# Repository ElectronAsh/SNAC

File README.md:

# SNAC
Accessory converter for MiSTer, by blue212

Serial Native Accessory Converter

SNAC is general purpose level shifter for use with MiSTer. It can be used to power 5v devices and it will safely convert any logic between the 3v3(MiSTer) and 5 device. It will be used mostly for 5v controllers and other peripherals.

The SNAC connects to the User port(formerly Serial I/O port) of the IO board on Mister. I recommend a male to female usb3 extension cable between them.

The SNAC is available in 2 versions the only difference being the connector on the controller side(USB3 or HDMI). Various adapters can then be plugged into that connector. I made various adapter PCCBs for use with the USB3 verrsion.

Becasue the SNAC connects to the User port the peripheral connects to the GPIO of the MiSTer, this bypasses all layers the normal usb controllers use. So it's very much like having a controller port for the original system. One benefit of this is that most weird peripherals should work with their cores(like Lightguns etc) which most normal usb converters either don't or can't do. One downside to bypassing the layers is the you can't controle the OSD.

*A mod to the IO board is needed if you want to use SEGA peripherals. A possible IO board revision in the future may fix this requirement.

-TODO detail the needed mod

-Updates

Changed the partslist to use a different part for the male USB connector.

Uxcell a19032000ux0260 instead of Wuerth 692112030100

Combined SNES versions, and SMS DB9 version added by ElectronAsh.

#Both SNES versions, and the SMS DB9 version are UNTESTED.
Please do not build until they are confirmed working.

Version with JST XH for the USER IO connection, and PCB meant for a specific housing.
You can find the housing on eBay, using the search term "enclosure 90x70x28mm"

The 3D Glasses driver circuit is from e-panorama...
<https://www.epanorama.net/circuits/sega3d.html>

The circuit has been tested on the SMS core now, but it needs a charge pump circuit added, to boost the LCD drive voltage to around 10 Volts.
Without that, the LCDs don't darken enough, and the ghosting is quite severe.

I tested the circuit by powering the CD4030 chip with 10V from a bench PSU. 
(That should ONLY be done if you completely isolate that 10V from the 5V pin on the USER PORT, otherwise it will damage the DE10 Nano.)

EDIT: A charge pump circuit has been added to both the DB9 and dongle version of the 3D Glasses adapter now.
This is currently UNTESTED until more PCBs arrive.

The dongle was tested with the Asus VR-100G LCD shutter glasses, and a JVC monitor.
The frequency of the oscillator that drives the LCDs doesn't seem to have any particular sweet spot for reduction ghosting, but the circuit generally works fine.

The standalone dongle version of the 3D Glasses driver is for people who don't mind using the SMS core with a USB joypad, and just want the 3D glasses option.
(in which case, both SMS buttons will obviously work fine when mapping from a USB joypad, or USB keyboard.)

I updated the SMS core repo on my github with a new menu options (in the Input section) for SNAC-Only, 3D-Only, or SNAC+3D.

<https://github.com/ElectronAsh/SMS_MiSTer/blob/f2dcc660f143cf5afca576f203ca9adbdb81673e/SMS.sv#L199>

One caveat of the 3D mode is that the signal normally used for the Button 2 input from the SMS joypad is used to control the 3D glasses.
So Button 2 won't work in games when 3D glasses mode is enabled.

This also means the option for the "Pause Button Combo" won't work either via SNAC (real SMS joypad) with 3D glasses mode enabled, and the Pause option will be greyed out in the OSD.
(But you can still use the Pause button mapping from a USB joypad.)

AFAIK, SMS Light Gun support should still work via the SNAC adapter with 3D Glasses enabled, but this is currently UNTESTED.
I believe Missile Command 3-D is one of the few SMS games to support 3D Glasses and the Light Gun at the same time.

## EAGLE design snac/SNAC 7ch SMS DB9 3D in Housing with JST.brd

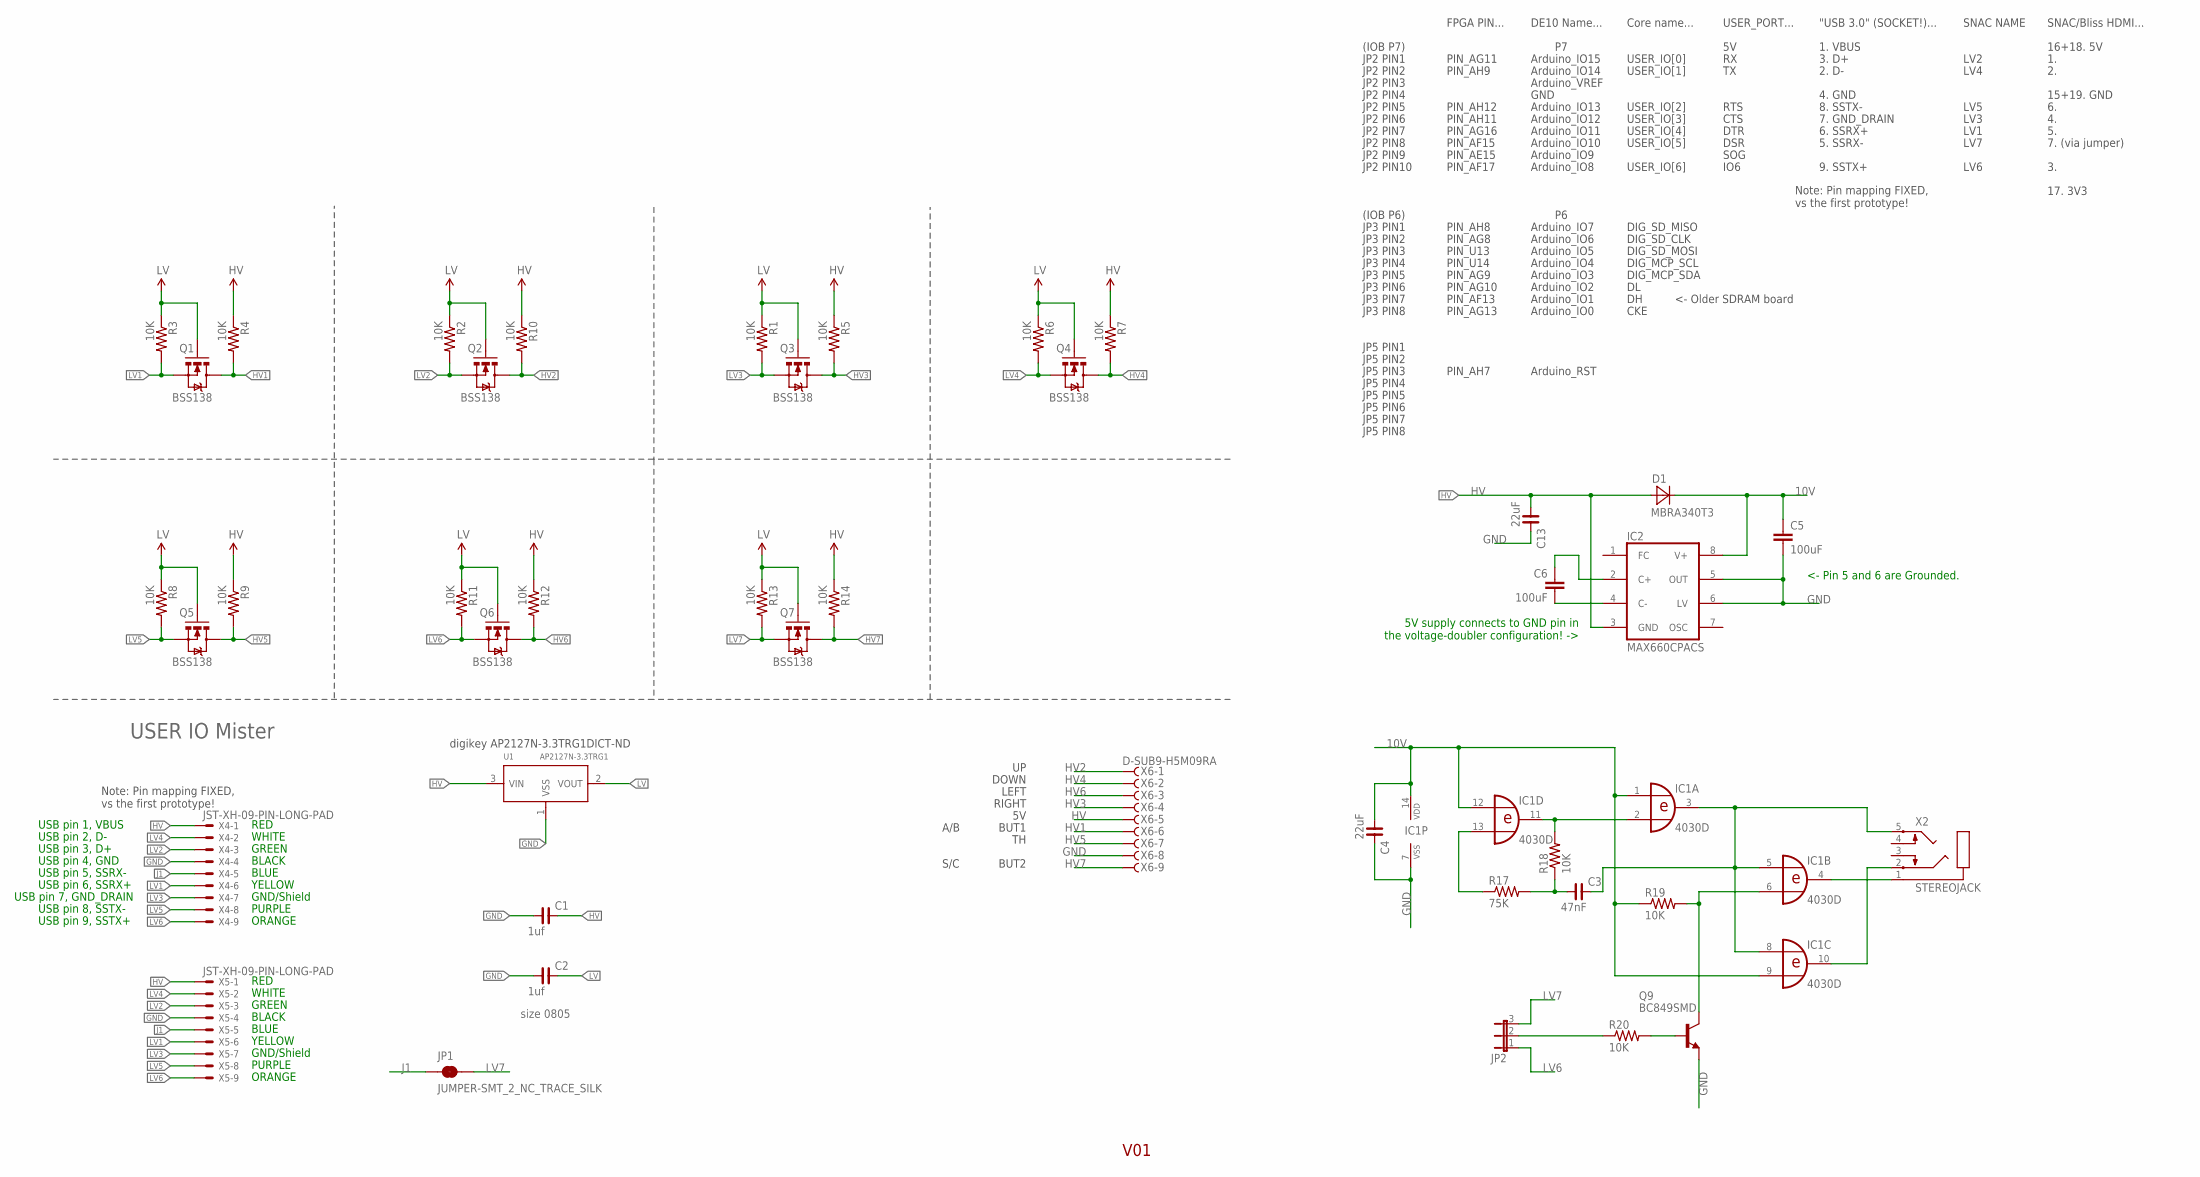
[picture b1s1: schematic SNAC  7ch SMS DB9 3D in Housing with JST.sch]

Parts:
C1, C2: 1uf; C0805
C3: 47nF; C0805
C4, C13: 22uF; C0805
C5, C6: 100uF; C1812
D1: MBRA340T3; SMA
IC1: 4030D; SO14
IC2: MAX660CPACS; SO08
JP1: JUMPER-SMT_2_NC_TRACE_SILK; SMT-JUMPER_2_NC_TRACE_SILK
JP2: JP2E; JP2
Q1, Q2, Q3, Q4, Q5, Q6, Q7: BSS138; SOT23-3
Q9: BC849SMD; SOT23-BEC
R1, R2, R3, R4, R5, R6, R7, R8, R9, R10, R11, R12, R13, R14, R18, R19, R20: 10K; 0603-RES
R17: 75K; 0603-RES
U1: AP2127N-3.3TRG1; SOT-23
X2: STEREOJACK; STX3100
X4, X5: JST-XH-09-PIN-LONG-PAD; JST-XH-09-PACKAGE-LONG-PAD
X6: D-SUB9-H5M09RA; H5M09RA

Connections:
10V: C4.1, C5.1, D1.C, IC1.1 (I0), IC1.9 (I1), IC1.12 (I0), IC1.14 (VDD), IC2.8 (V+), R19.1
GND: C1.1, C2.1, C4.2, C5.2, C13.2, IC1.7 (VSS), IC2.5 (OUT), IC2.6 (LV), Q9.E, U1.1 (VSS), X4.4, X5.4, X6.8
HV: C1.2, C13.1, D1.A, IC2.3 (GND), R4.1, R5.1, R7.1, R9.1, R10.1, R12.1, R14.1, U1.3 (VIN), X4.1, X5.1, X6.5
HV1: Q1.3 (D), R4.2, X6.6
HV2: Q2.3 (D), R10.2, X6.1
HV3: Q3.3 (D), R5.2, X6.4
HV4: Q4.3 (D), R7.2, X6.2
HV5: Q5.3 (D), R9.2, X6.7
HV6: Q6.3 (D), R12.2, X6.3
HV7: Q7.3 (D), R14.2, X6.9
J1: JP1.1, X4.5, X5.5
LV: C2.2, Q1.1 (G), Q2.1 (G), Q3.1 (G), Q4.1 (G), Q5.1 (G), Q6.1 (G), Q7.1 (G), R1.1, R2.1, R3.1, R6.1, R8.1, R11.1, R13.1, U1.2 (VOUT)
LV1: Q1.2 (S), R3.2, X4.6, X5.6
LV2: Q2.2 (S), R2.2, X4.3, X5.3
LV3: Q3.2 (S), R1.2, X4.7, X5.7
LV4: Q4.2 (S), R6.2, X4.2, X5.2
LV5: Q5.2 (S), R8.2, X4.8, X5.8
LV6: JP2.1, Q6.2 (S), R11.2, X4.9, X5.9
LV7: JP1.2, JP2.3, Q7.2 (S), R13.2
unnamed: IC1.2 (I1), IC1.11 (O), R18.2
unnamed: C3.2, IC1.3 (O), IC1.5 (I0), IC1.8 (I0), X2.5
unnamed: IC1.4 (O), X2.1
unnamed: IC1.10 (O), X2.2
unnamed: IC1.13 (I1), R17.1
unnamed: C6.1, IC2.2 (C+)
unnamed: IC1.6 (I1), Q9.C, R19.2
unnamed: Q9.B, R20.2
unnamed: C6.2, IC2.4 (C-)
unnamed: C3.1, R17.2, R18.1
unnamed: JP2.2, R20.1

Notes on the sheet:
V01
size 0805
DOWN
LEFT
RIGHT
BUT1
BUT2
A/B
S/C
USER IO Mister
USB pin 2, D-
USB pin 3, D+
USB pin 5, SSRX-
USB pin 6, SSRX+
USB pin 7, GND_DRAIN
USB pin 1, VBUS
USB pin 8, SSTX-
USB pin 9, SSTX+
USB pin 4, GND
RED
WHITE
GREEN
BLACK
BLUE
YELLOW
GND/Shield
PURPLE
ORANGE
5V supply connects to GND pin in the voltage-doubler configuration! ->
<- Pin 5 and 6 are Grounded.
digikey AP2127N-3.3TRG1DICT-ND
JP2 PIN1
PIN_AH7
JP2 PIN2
JP2 PIN3
JP2 PIN4
JP2 PIN5
JP2 PIN6
JP2 PIN7
JP2 PIN8

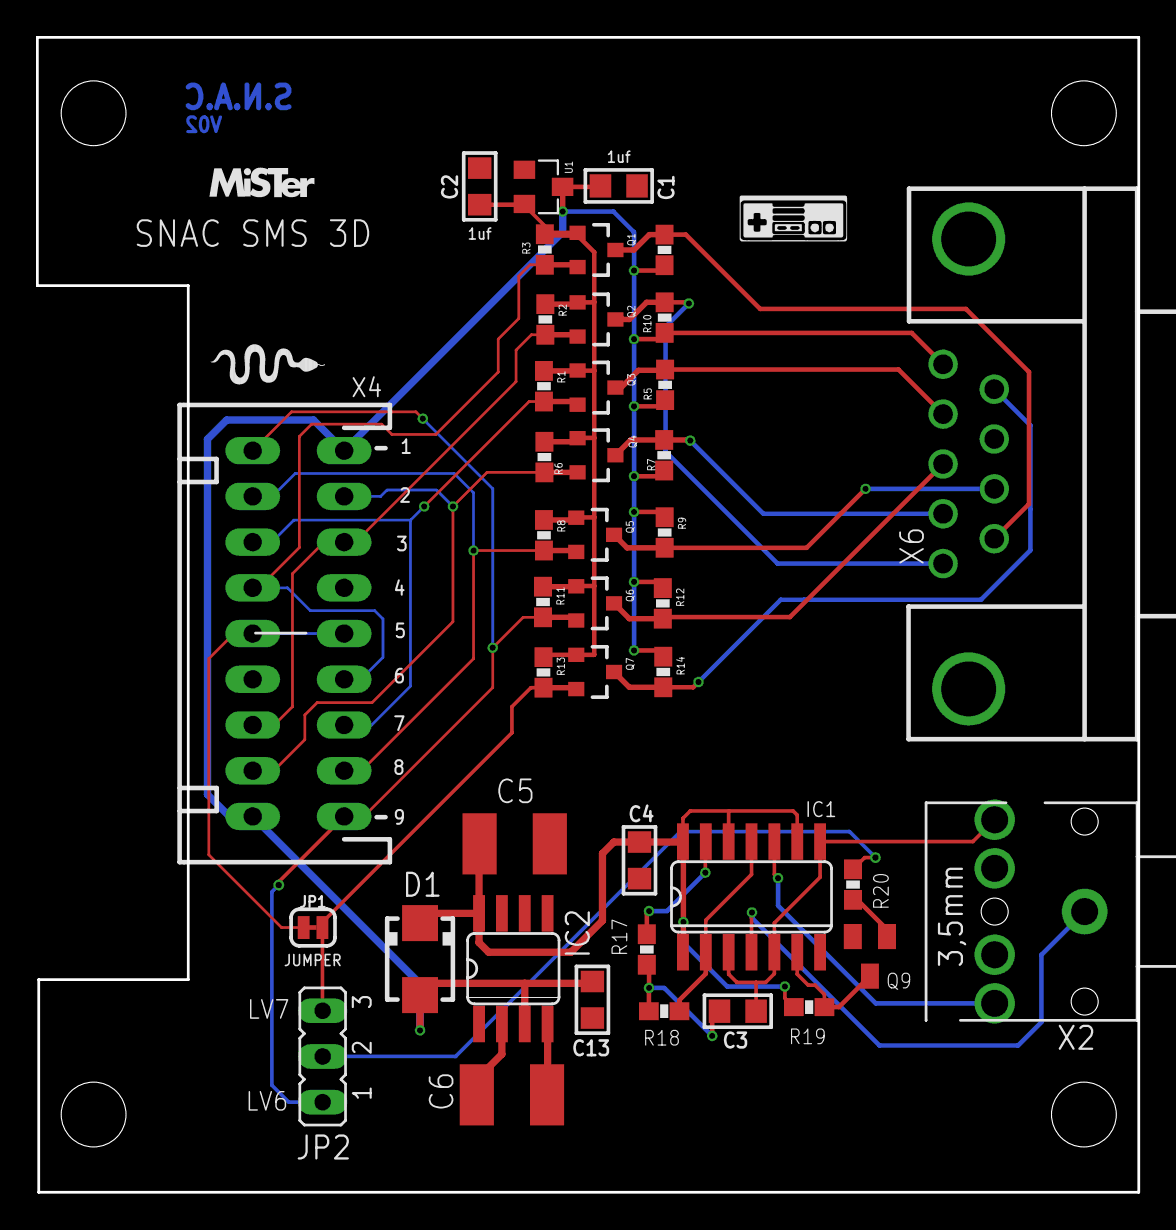
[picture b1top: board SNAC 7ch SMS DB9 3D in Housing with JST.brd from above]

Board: 2 copper layers, 61.2 x 64.2 mm, 43 parts (1 on the bottom side), 30 nets.

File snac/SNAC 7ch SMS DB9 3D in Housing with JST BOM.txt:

digiPartlist exported from C:/SNAC/snac/SNAC  7ch SMS DB9 3D in Housing with JST.sch at 16/04/2021 22:44

Part Value                          Device                         Package                     Description 
C1   1uf                            C_0805                         C0805                       NON-POLARIZED CAP	                    digikey 732-7625-1-ND
C2   1uf                            C_0805                         C0805                       NON-POLARIZED CAP	                    digikey 732-7625-1-ND
C3   47nF                           C_0805                         C0805                       NON-POLARIZED CAP	                    digikey 399-C0805C473K2RECAUTOCT-ND
C4   22uF                           C_0805                         C0805                       NON-POLARIZED CAP                        digikey 399-4696-1-ND‎
C5   100uF                          C-EUC1812                      C1812                       CAPACITOR, European symbol               digikey ‎445-7743-1-ND‎
C6   100uF                          C-EUC1812                      C1812                       CAPACITOR, European symbol               digikey ‎445-7743-1-ND‎
C13  22uF                           C_0805                         C0805                       NON-POLARIZED CAP                        digikey 399-4696-1-ND‎
D1   MBRA160T3G‎                     MBRA160T3G‎                     SMA                         Surface Mount Schottky Power Rectifier   digikey MBRA160T3GOSCT-ND
IC1  4030D                          4030D                          SO14                        Quad XOR                                 digikey 296-14263-5-ND
IC2  MAX660CPACS                    MAX660CPACS                    SO08                        Charge-pump VOLTAGE CONVERTER            digikey MAX660MX/NOPBCT-ND
Q1   BSS138                         MOSFET-NCHANNELSMD             SOT23-3                                                              digikey BSS138LCT-ND
Q2   BSS138                         MOSFET-NCHANNELSMD             SOT23-3                                                              digikey BSS138LCT-ND
Q3   BSS138                         MOSFET-NCHANNELSMD             SOT23-3                                                              digikey BSS138LCT-ND
Q4   BSS138                         MOSFET-NCHANNELSMD             SOT23-3                                                              digikey BSS138LCT-ND
Q5   BSS138                         MOSFET-NCHANNELSMD             SOT23-3                                                              digikey BSS138LCT-ND
Q6   BSS138                         MOSFET-NCHANNELSMD             SOT23-3                                                              digikey BSS138LCT-ND
Q7   BSS138                         MOSFET-NCHANNELSMD             SOT23-3                                                              digikey BSS138LCT-ND
Q9   BC849SMD                       BC849SMD                       SOT23-BEC                   NPN Transistor                           digikey BC847C-TPCT-ND
R1   10K                            RESISTOR0603-RES               0603-RES                    Resistor                                 digikey RMCF0603FT10K0CT-ND‎
R2   10K                            RESISTOR0603-RES               0603-RES                    Resistor                                 digikey RMCF0603FT10K0CT-ND‎
R3   10K                            RESISTOR0603-RES               0603-RES                    Resistor                                 digikey RMCF0603FT10K0CT-ND
R4   10K                            RESISTOR0603-RES               0603-RES                    Resistor                                 digikey RMCF0603FT10K0CT-ND
R5   10K                            RESISTOR0603-RES               0603-RES                    Resistor                                 digikey RMCF0603FT10K0CT-ND
R6   10K                            RESISTOR0603-RES               0603-RES                    Resistor                                 digikey RMCF0603FT10K0CT-ND
R7   10K                            RESISTOR0603-RES               0603-RES                    Resistor                                 digikey RMCF0603FT10K0CT-ND
R8   10K                            RESISTOR0603-RES               0603-RES                    Resistor                                 digikey RMCF0603FT10K0CT-ND
R9   10K                            RESISTOR0603-RES               0603-RES                    Resistor                                 digikey RMCF0603FT10K0CT-ND
R10  10K                            RESISTOR0603-RES               0603-RES                    Resistor                                 digikey RMCF0603FT10K0CT-ND
R11  10K                            RESISTOR0603-RES               0603-RES                    Resistor                                 digikey RMCF0603FT10K0CT-ND
R12  10K                            RESISTOR0603-RES               0603-RES                    Resistor                                 digikey RMCF0603FT10K0CT-ND
R15  10K                            RESISTOR0603-RES               0603-RES                    Resistor                                 digikey RMCF0603FT10K0CT-ND
R16  10K                            RESISTOR0603-RES               0603-RES                    Resistor                                 digikey RMCF0603FT10K0CT-ND
R17  75K                            RESISTOR0603-RES               0603-RES                    Resistor                                 digikey RMCF0603JT75K0CT-ND
R18  10K                            RESISTOR0603-RES               0603-RES                    Resistor                                 digikey RMCF0603FT10K0CT-ND
R19  10K                            RESISTOR0603-RES               0603-RES                    Resistor                                 digikey RMCF0603FT10K0CT-ND
R20  10K                            RESISTOR0603-RES               0603-RES                    Resistor                                 digikey RMCF0603FT10K0CT-ND
U1   AP2127N-3.3TRG1                LDO 3V3                        SOT-23                      Voltage Regulator                        digikey AP2127N-3.3TRG1DICT-ND
X2   STEREOJACK                     STEREOJACK                     STX3100                     MIC/HEADPHONE JACK                       digikey CP1-3523N-ND
X4   JST-XH-09-PIN-LONG-PAD         JST-XH-09-PIN-LONG-PAD         JST-XH-09-PACKAGE-LONG-PAD  JST XH Connector 9 Pin                   digikey 455-2224-ND
X5   JST-XH-09-PIN-LONG-PAD         JST-XH-09-PIN-LONG-PAD         JST-XH-09-PACKAGE-LONG-PAD  JST XH Connector 9 Pin                   (only need one 9-pin JST)
X6   D-SUB9-H5M09RA                 D-SUB9-H5M09RA                 H5M09RA                     D-Subminiature Connector                 digikey 609-5183-ND

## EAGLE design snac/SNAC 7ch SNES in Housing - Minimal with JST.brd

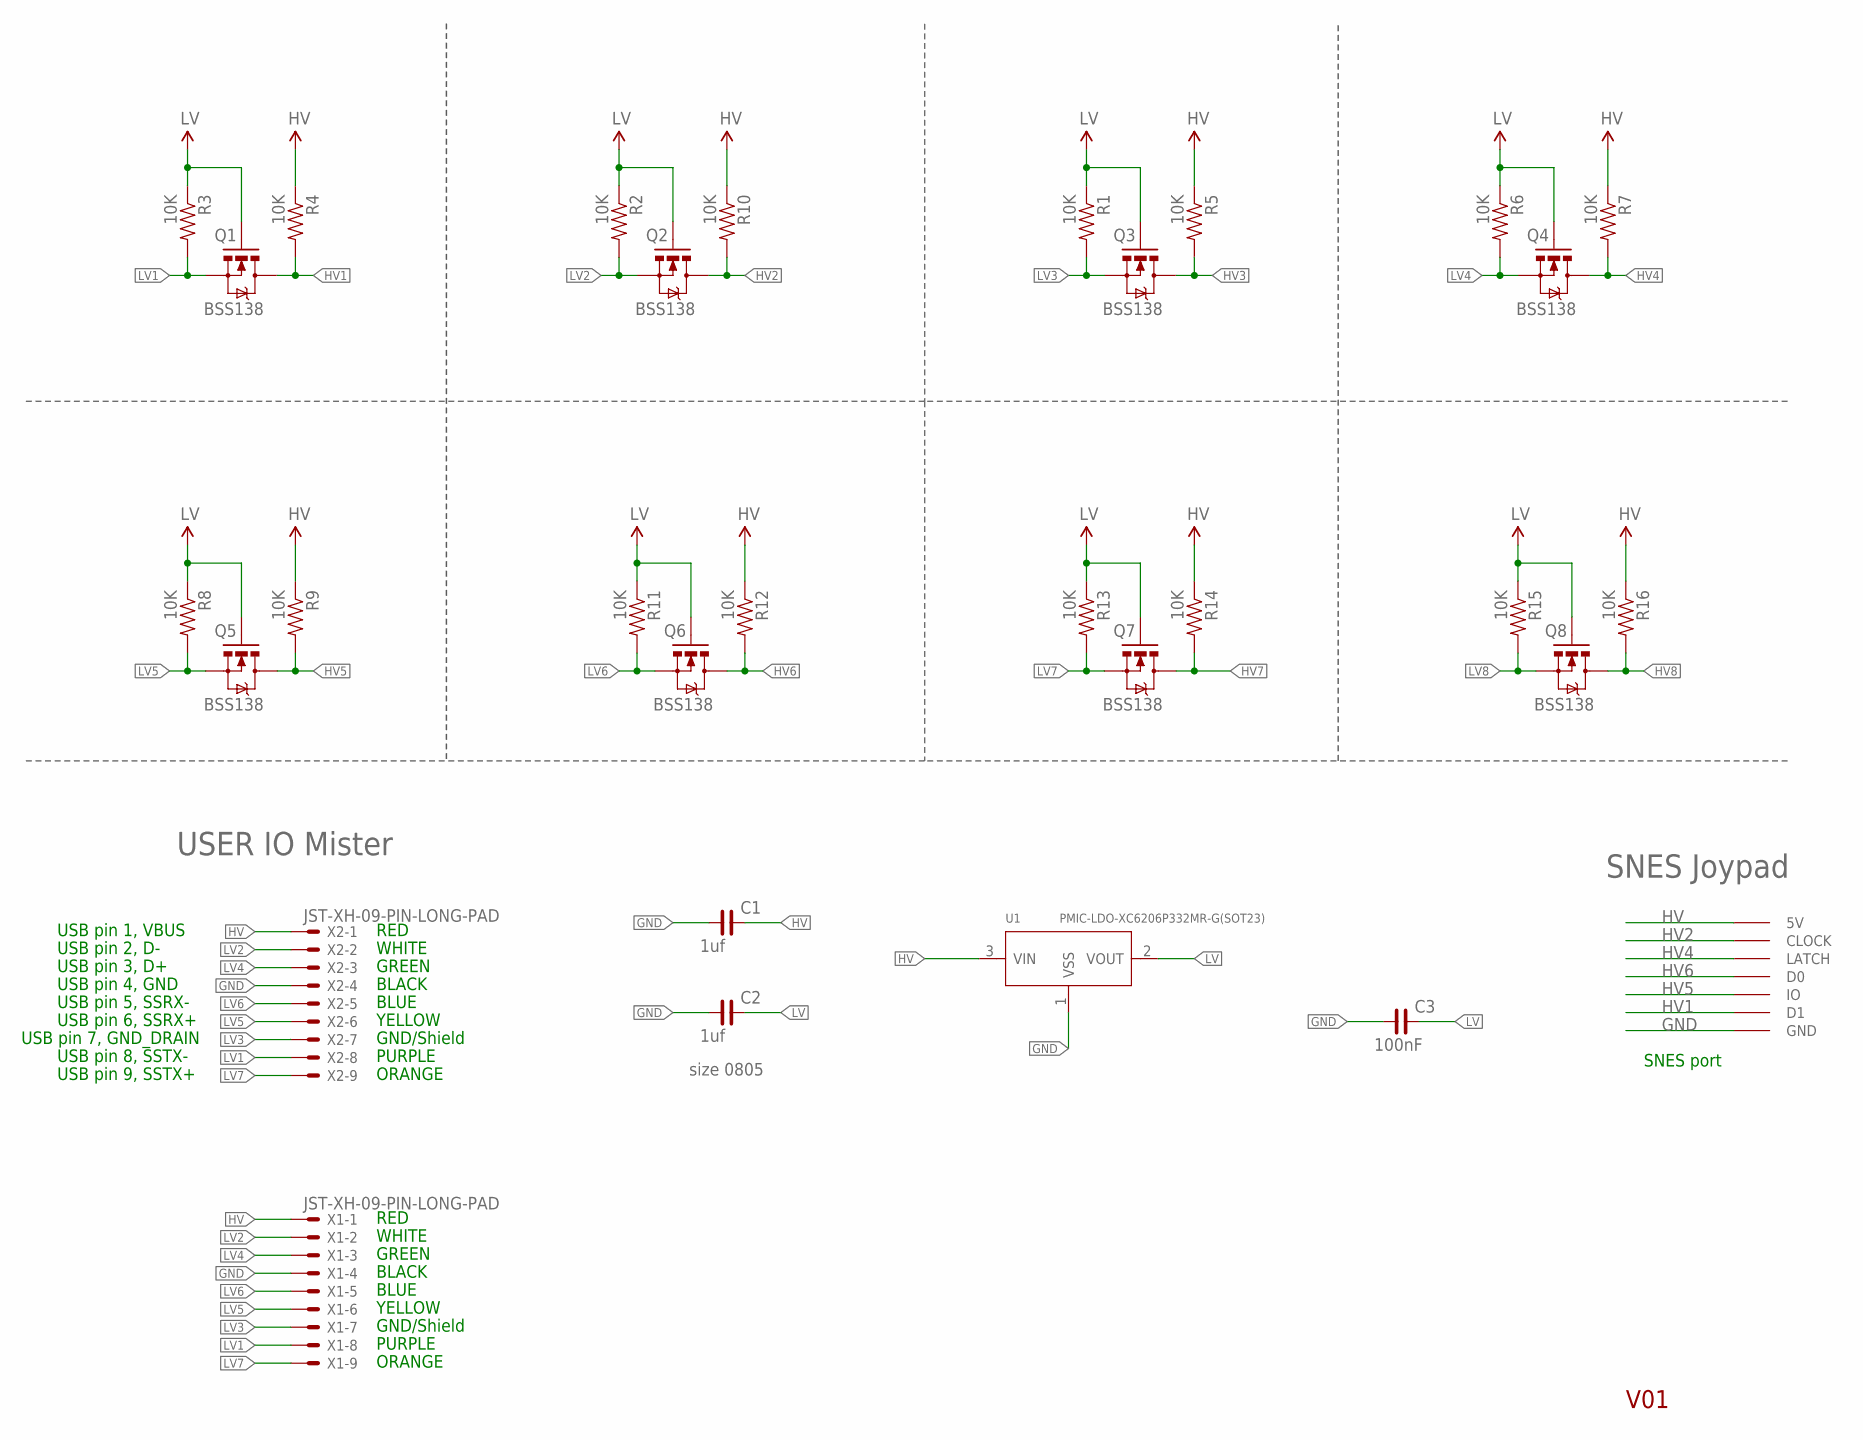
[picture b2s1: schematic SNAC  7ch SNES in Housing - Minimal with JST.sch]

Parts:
C1, C2: 1uf; C0805
C3: 100nF; C0805
Q1, Q2, Q3, Q4, Q5, Q6, Q7, Q8: BSS138; SOT23-3
R1, R2, R3, R4, R5, R6, R7, R8, R9, R10, R11, R12, R13, R14, R15, R16: 10K; 0603-RES
SNES_CON: SNESCONN
U1: PMIC-LDO-XC6206P332MR-G(SOT23); SOT-23
X1, X2: JST-XH-09-PIN-LONG-PAD; JST-XH-09-PACKAGE-LONG-PAD

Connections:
GND: C1.1, C2.1, C3.1, SNES_CON.GND, U1.1 (VSS), X1.4, X2.4
HV: C1.2, R4.1, R5.1, R7.1, R9.1, R10.1, R12.1, R14.1, R16.1, SNES_CON.5V, U1.3 (VIN), X1.1, X2.1
HV1: Q1.3 (D), R4.2, SNES_CON.D1
HV2: Q2.3 (D), R10.2, SNES_CON.CLOCK
HV3: Q3.3 (D), R5.2
HV4: Q4.3 (D), R7.2, SNES_CON.LATCH
HV5: Q5.3 (D), R9.2, SNES_CON.IO
HV6: Q6.3 (D), R12.2, SNES_CON.D0
HV7: Q7.3 (D), R14.2
HV8: Q8.3 (D), R16.2
LV: C2.2, C3.2, Q1.1 (G), Q2.1 (G), Q3.1 (G), Q4.1 (G), Q5.1 (G), Q6.1 (G), Q7.1 (G), Q8.1 (G), R1.1, R2.1, R3.1, R6.1, R8.1, R11.1, R13.1, R15.1, U1.2 (VOUT)
LV1: Q1.2 (S), R3.2, X1.8, X2.8
LV2: Q2.2 (S), R2.2, X1.2, X2.2
LV3: Q3.2 (S), R1.2, X1.7, X2.7
LV4: Q4.2 (S), R6.2, X1.3, X2.3
LV5: Q5.2 (S), R8.2, X1.6, X2.6
LV6: Q6.2 (S), R11.2, X1.5, X2.5
LV7: Q7.2 (S), R13.2, X1.9, X2.9
LV8: Q8.2 (S), R15.2

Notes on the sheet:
V01
USER IO Mister
size 0805
SNES port
SNES Joypad
USB pin 2, D-
USB pin 3, D+
USB pin 5, SSRX-
USB pin 6, SSRX+
USB pin 7, GND_DRAIN
USB pin 1, VBUS
USB pin 8, SSTX-
USB pin 9, SSTX+
USB pin 4, GND
RED
WHITE
GREEN
BLACK
BLUE
YELLOW
GND/Shield
PURPLE
ORANGE

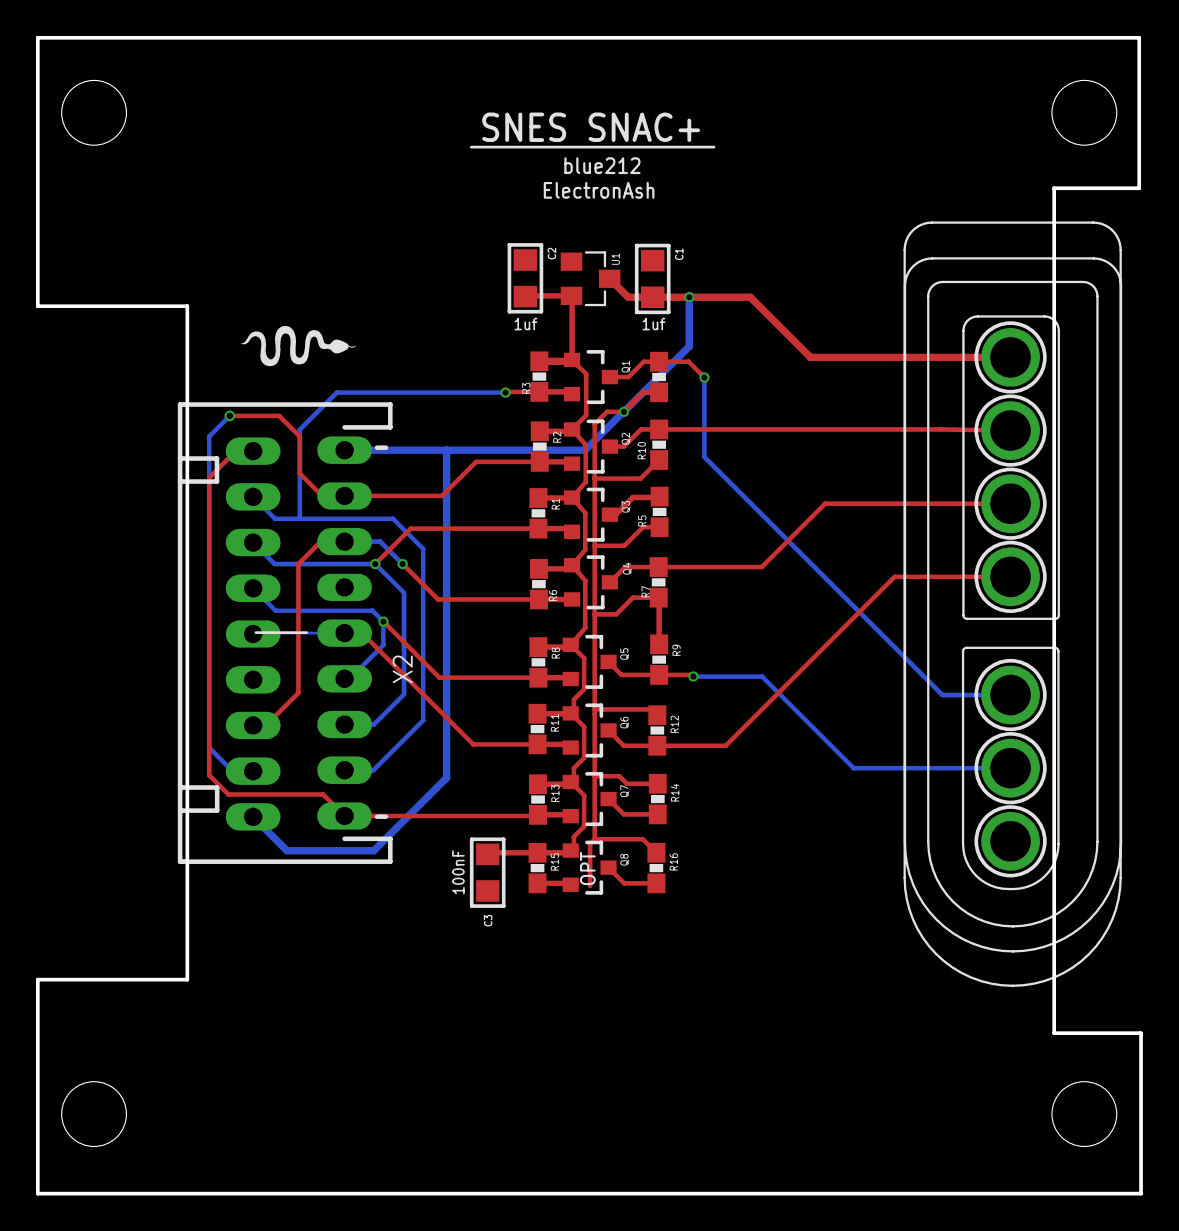
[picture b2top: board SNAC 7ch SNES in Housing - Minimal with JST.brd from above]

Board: 2 copper layers, 61.3 x 64.2 mm, 31 parts (1 on the bottom side), 19 nets.

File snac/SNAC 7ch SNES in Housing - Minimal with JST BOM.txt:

Partlist exported from C:/SNAC/snac/SNAC  7ch SNES in Housing - Minimal with JST.sch at 26/04/2021 04:11

Part     Value                          Device                         Package                    Description            AVAILABILITY DESCRIPTION MF   MP      PACKAGE PRICE 
C1       1uf                            C_0805                         C0805                      NON-POLARIZED CAP                                                          
C2       1uf                            C_0805                         C0805                      NON-POLARIZED CAP                                                          
C3       100nF                          C_0805                         C0805                      NON-POLARIZED CAP                                                          
Q1       BSS138                         MOSFET-NCHANNELSMD             SOT23-3                                                                                               
Q2       BSS138                         MOSFET-NCHANNELSMD             SOT23-3                                                                                               
Q3       BSS138                         MOSFET-NCHANNELSMD             SOT23-3                                                                                               
Q4       BSS138                         MOSFET-NCHANNELSMD             SOT23-3                                                                                               
Q5       BSS138                         MOSFET-NCHANNELSMD             SOT23-3                                                                                               
Q6       BSS138                         MOSFET-NCHANNELSMD             SOT23-3                                                                                               
Q7       BSS138                         MOSFET-NCHANNELSMD             SOT23-3                                                                                               
Q8       BSS138                         MOSFET-NCHANNELSMD             SOT23-3                                                                                               
R1       10K                            RESISTOR0603-RES               0603-RES                   Resistor                                                                   
R2       10K                            RESISTOR0603-RES               0603-RES                   Resistor                                                                   
R3       10K                            RESISTOR0603-RES               0603-RES                   Resistor                                                                   
R4       10K                            RESISTOR0603-RES               0603-RES                   Resistor                                                                   
R5       10K                            RESISTOR0603-RES               0603-RES                   Resistor                                                                   
R6       10K                            RESISTOR0603-RES               0603-RES                   Resistor                                                                   
R7       10K                            RESISTOR0603-RES               0603-RES                   Resistor                                                                   
R8       10K                            RESISTOR0603-RES               0603-RES                   Resistor                                                                   
R9       10K                            RESISTOR0603-RES               0603-RES                   Resistor                                                                   
R10      10K                            RESISTOR0603-RES               0603-RES                   Resistor                                                                   
R11      10K                            RESISTOR0603-RES               0603-RES                   Resistor                                                                   
R12      10K                            RESISTOR0603-RES               0603-RES                   Resistor                                                                   
R13      10K                            RESISTOR0603-RES               0603-RES                   Resistor                                                                   
R14      10K                            RESISTOR0603-RES               0603-RES                   Resistor                                                                   
R15      10K                            RESISTOR0603-RES               0603-RES                   Resistor                                                                   
R16      10K                            RESISTOR0603-RES               0603-RES                   Resistor                                                                   
SNES_CON SNESCONN                       SNESCONN                       SNESCONN                                                                                              
U1       PMIC-LDO-XC6206P332MR-G(SOT23) PMIC-LDO-XC6206P332MR-G(SOT23) SOT-23                     310030099              Unavailable   SMD PMIC    LDO  Vin 6V  3.3V    200mA
X1       JST-XH-09-PIN-LONG-PAD         JST-XH-09-PIN-LONG-PAD         JST-XH-09-PACKAGE-LONG-PAD JST XH Connector 2 Pin                                                     
X2       JST-XH-09-PIN-LONG-PAD         JST-XH-09-PIN-LONG-PAD         JST-XH-09-PACKAGE-LONG-PAD JST XH Connector 2 Pin

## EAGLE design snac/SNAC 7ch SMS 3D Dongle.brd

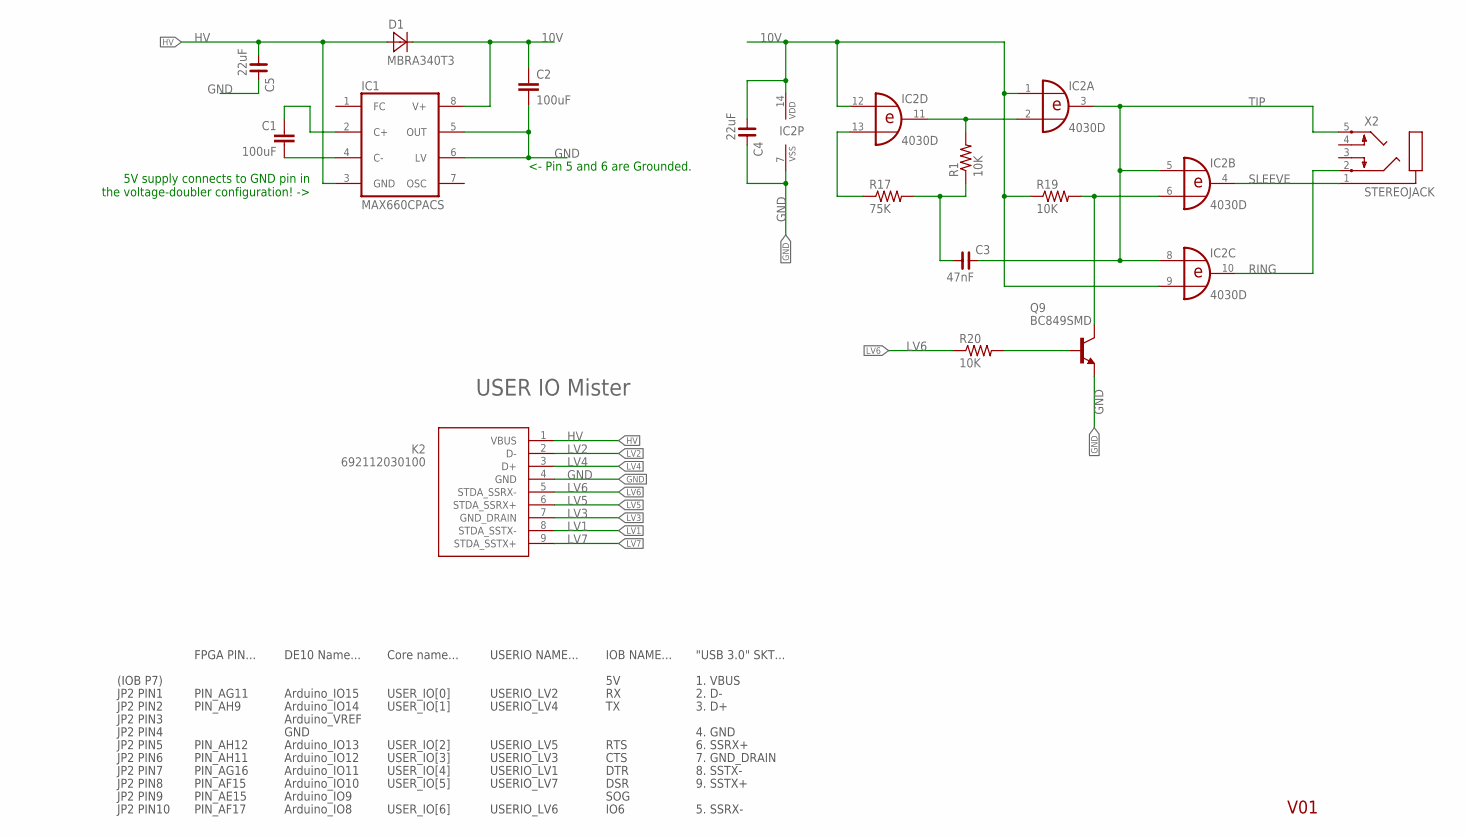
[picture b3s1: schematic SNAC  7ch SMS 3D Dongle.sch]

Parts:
C1, C2: 100uF; C1210
C3: 47nF; C0805
C4, C5: 22uF; C0805
D1: MBRA340T3; SMA
IC1: MAX660CPACS; SO08
IC2: 4030D; SO14
K2: 692112030100
Q9: BC849SMD; SOT23-BEC
R1, R19, R20: 10K; 0603-RES
R17: 75K; 0603-RES
X2: STEREOJACK; STX3100

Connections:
10V: C2.1, C4.1, D1.C, IC1.8 (V+), IC2.1 (I0), IC2.9 (I1), IC2.12 (I0), IC2.14 (VDD), R19.1
GND: C2.2, C4.2, C5.2, IC1.5 (OUT), IC1.6 (LV), IC2.7 (VSS), K2.4 (GND), Q9.E
HV: C5.1, D1.A, IC1.3 (GND), K2.1 (VBUS)
LV1: K2.8 (STDA_SSTX-)
LV2: K2.2 (D-)
LV3: K2.7 (GND_DRAIN)
LV4: K2.3 (D+)
LV5: K2.6 (STDA_SSRX+)
LV6: K2.5 (STDA_SSRX-), R20.1
LV7: K2.9 (STDA_SSTX+)
unnamed: C3.1, R1.1, R17.2
unnamed: IC2.2 (I1), IC2.11 (O), R1.2
unnamed: IC2.13 (I1), R17.1
unnamed: IC2.6 (I1), Q9.C, R19.2
unnamed: Q9.B, R20.2
unnamed: C1.1, IC1.2 (C+)
unnamed: C1.2, IC1.4 (C-)
RING: IC2.10 (O), X2.2
SLEEVE: IC2.4 (O), X2.1
TIP: C3.2, IC2.3 (O), IC2.5 (I0), IC2.8 (I0), X2.5

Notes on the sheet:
V01
USER IO Mister
Arduino_IO15
Arduino_IO14
Arduino_IO13
Arduino_VREF
Arduino_IO12
Arduino_IO11
Arduino_IO10
Arduino_IO9
Arduino_IO8
RTS
CTS
DTR
DSR
SOG
IO6
IOB NAME...
GND
2. D-
3. D+
4. GND
1. VBUS
5. SSRX-
6. SSRX+
7. GND_DRAIN
8. SSTX-
9. SSTX+
"USB 3.0" SKT...
DE10 Name...
Core name...
USER_IO[6]
USER_IO[5]
USER_IO[4]
USER_IO[3]
USER_IO[2]
USER_IO[1]
USER_IO[0]
JP2 PIN1
USERIO_LV2

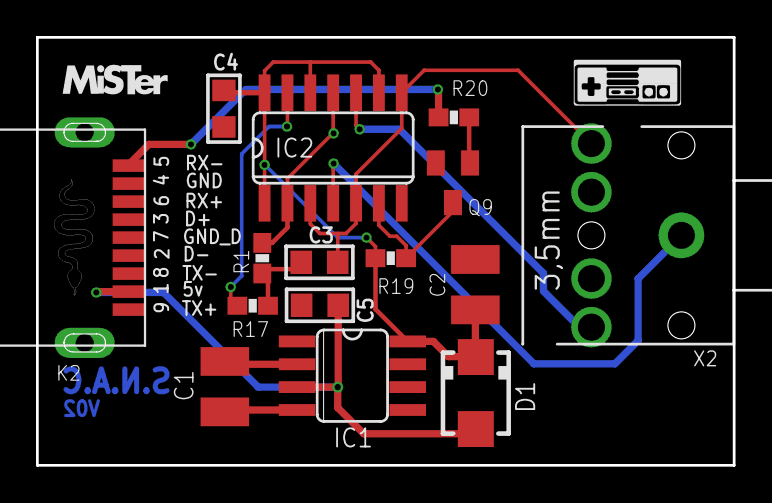
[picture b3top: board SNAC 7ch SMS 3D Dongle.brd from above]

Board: 2 copper layers, 38.7 x 23.8 mm, 15 parts (0 on the bottom side), 14 nets.

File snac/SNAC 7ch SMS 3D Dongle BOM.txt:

Partlist exported from C:/SNAC/snac/SNAC  7ch SMS 3D Dongle.sch at 09/12/2020 16:54

Part Value        Device           Package      Description
R17  75K          RESISTOR0603-RES 0603-RES     Resistor                                 digikey RMCF0603FT75K0
R1   10K          RESISTOR0603-RES 0603-RES     Resistor                                 digikey RMCF0603JT10K0CT-ND
R19  10K          RESISTOR0603-RES 0603-RES     Resistor                                 digikey RMCF0603JT10K0CT-ND
R20  10K          RESISTOR0603-RES 0603-RES     Resistor                                 digikey RMCF0603JT10K0CT-ND
C1   100uF        C_1210           C1210        NON-POLARIZED CAP 16V                    digikey EMK325ABJ107MM-P
C2   100uF        C_1210           C1210        NON-POLARIZED CAP 16V                    digikey EMK325ABJ107MM-P
C3   10nF         C_0805           C0805        NON-POLARIZED CAP                        digikey C0805X103K1RAC3316CT-ND
C4   22uF         C_0805           C0805        NON-POLARIZED CAP                        digikey 399-4696-1-ND
C5   22uF         C_0805           C0805        NON-POLARIZED CAP                        digikey 399-4696-1-ND
D1   MBRA340T3    MBRA340T3        SMA          Schottky Diode                           digikey 2156-MBRA340T3G-OS-ND
IC1  MAX660MX     MAX660           SO8          Charge Pump IC                           digikey MAX660MX/NOPBCT-ND
IC2  4030D        4030D            SO14         Quad XOR                                 digikey 296-14263-5-ND
Q9   BC849SMD     BC849SMD         SOT23-BEC    NPN Transistor                           digikey BC847C-TPCT-ND
X2   STEREOJACK   STEREOJACK       STX3100      MIC/HEADPHONE JACK                       digikey CP1-3523N-ND
K2   692112030100 692112030100     692112030100 WR-COM  USB 3.0 SMT PLUG WITH CLIPTYPE A digikey 732-3157-ND

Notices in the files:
parts and their libraries:
Wuerth_Elektronik_eiCan_Communication_Co: Copyright: Würth Elektronik
rc-master-smd: Copyright (C) 2007, Bob Starr
SparkFun-Jumpers: Licensing: Creative Commons ShareAlike 4.0 International - https://creativecommons.org/licenses/by-sa/4.0
